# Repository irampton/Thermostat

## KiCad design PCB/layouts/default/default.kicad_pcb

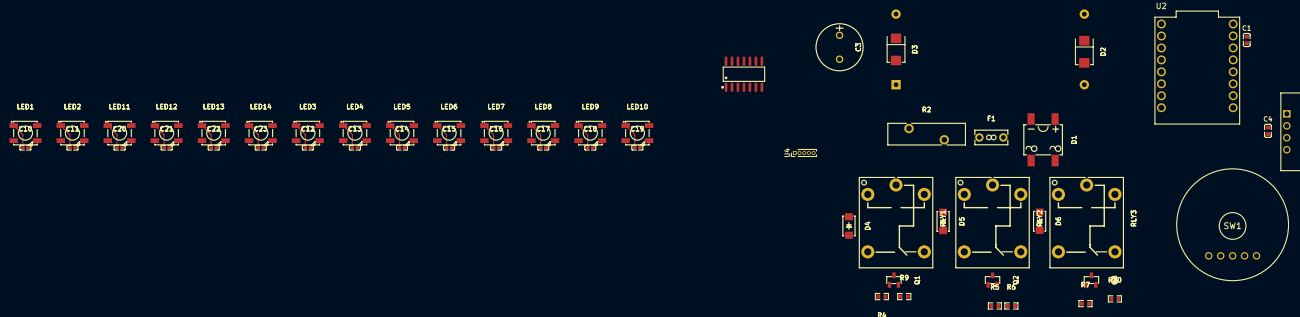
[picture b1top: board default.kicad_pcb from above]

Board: 2 copper layers, 57 parts (1 on the bottom side), 38 nets.

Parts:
C1, C4: 100nF ±10% 50V X7R; C0603
C3: 470µF ±20% 50V; CAP-TH_BD10.0-P5.00-D1.0-FD
C10, C11, C12, C13, C14, C15, C16, C17, C18, C19, C20, C21, C22, C23: 100nF ±10% 50V X7R; C0402
D1: DBS_L8.2-W6.4-P5.10-LS10.0-TL
D2, D3: SMB_L4.6-W3.6-LS5.3-RD
D4, D5, D6: SMA_L4.2-W2.6-LS5.0-RD_1
F1: FUSE-TH_L7.0-W3.1-P5.08-D1.2
LED1, LED2, LED3, LED4, LED5, LED6, LED7, LED8, LED9, LED10, LED11, LED12, LED13, LED14: LED-SMD_4P-L5.0-W5.0-TL-1
Q1, Q2, Q3: SOT-23-3_L2.9-W1.3-P1.90-LS2.4-BR
R2: RES-TH_L16.5-W4.6-P7.50-D0.8-S2.40
R4, R5, R7: 100kΩ ±1% 100mW; R0603
R6, R9, R10: 1kΩ ±1% 100mW; R0603
RLY1, RLY2, RLY3: RELAY-TH_SRD-XXVDC-XL-C
SW1: ROUND_ROTARY
U1: AHT20
U2: ESP32C3-supermini
U3: LM2596_bord
U4: HVACHeader5Pin
U5: SOIC-14_L8.7-W3.9-P1.27-LS6.0-BL

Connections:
P1Y: LED1.4, U5.3
SCL: U1.SCL, U2.3
SDA: U1.SDA, U2.2
b: SW1.S1, U2.5
bleed_res-a-0: Q1.1, R4.1, R9.2
bleed_res-a-1: Q2.1, R5.1, R6.2
bleed_res-a-2: Q3.1, R7.1, R10.2
body-coil_power-GND-0: D4.2, Q1.3, RLY1.2
body-coil_power-GND-1: D5.2, Q2.3, RLY2.2
body-coil_power-GND-2: D6.2, Q3.3, RLY3.2
cool: RLY1.5, U4.4
data_out-DIN: LED10.2, LED11.4
fan: RLY2.5, U4.5
gpio[4]-a: SW1.CLK, U2.4
heat: RLY3.5, U4.3
hot_in: D1.3, F1.2, R2.2, RLY1.3, RLY2.3, RLY3.3
led1-data_in-DIN: LED1.2, LED2.4
led2-data_in-DIN: LED2.2, LED3.4
led3-data_in-DIN: LED3.2, LED4.4
led4-data_in-DIN: LED4.2, LED5.4
led5-data_in-DIN: LED5.2, LED6.4
led6-data_in-DIN: LED6.2, LED7.4
led7-data_in-DIN: LED7.2, LED8.4
led8-data_in-DIN: LED8.2, LED9.4
led9-data_in-DIN: LED9.2, LED10.4
led11-data_in-DIN: LED11.2, LED12.4
led12-data_in-DIN: LED12.2, LED13.4
led13-data_in-DIN: LED13.2, LED14.4
neutral: D1.4, R2.1, U4.2
power: F1.1, U4.1
power-GND: C1.2, C3.2, C4.2, C10.2, C11.2, C12.2, C13.2, C14.2, C15.2, C16.2, C17.2, C18.2, C19.2, C20.2, C21.2, C22.2, C23.2, D1.2, D2.2, D3.2, LED1.3, LED2.3, LED3.3, LED4.3, LED5.3, LED6.3, LED7.3, LED8.3, LED9.3, LED10.3, LED11.3, LED12.3, LED13.3, LED14.3, Q1.2, Q2.2, Q3.2, R4.2, R5.2, R7.2, SW1.GND, U1.GND, U2.GND, U3.IN-, U3.OUT-, U5.1, U5.5, U5.7, U5.9, U5.12
power-VCC: C10.1, C11.1, C12.1, C13.1, C14.1, C15.1, C16.1, C17.1, C18.1, C19.1, C20.1, C21.1, C22.1, C23.1, D2.1, D4.1, D5.1, D6.1, LED1.1, LED2.1, LED3.1, LED4.1, LED5.1, LED6.1, LED7.1, LED8.1, LED9.1, LED10.1, LED11.1, LED12.1, LED13.1, LED14.1, RLY1.1, RLY2.1, RLY3.1, U2.p5V, U3.OUT+, U5.4, U5.10, U5.13, U5.14
power_3v3-VCC: C1.1, C4.1, SW1.VCC, U1.VDD, U2.p3V3
spi0_cs-control: R10.1, U2.7
spi0_miso-control: R6.1, U2.9
spi0_sclk-control: R9.1, U2.8
sw: SW1.S2, U2.6
vin_plus: C3.1, D1.1, D3.1, U3.IN+

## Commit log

2025-09-30 Swapped buck converter
2025-10-02 Started on layout
2025-10-02 Started placement and examined components
